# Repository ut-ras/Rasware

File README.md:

# Rasware
Rasware is a generic robotics library project for the EK-LM4F120XL Stellaris Launchpad, built on top of StellarisWare. It is intended to be used for UT RAS's Robotathon competition as well as general purpose robotics projects.
Authored by the IEEE - Robotics and Automation Society Student Branch at the University of Texas at Austin. For documentation, see Rasware's Github [wiki](https://github.com/ut-ras/Rasware/wiki).

---
# Robotathon Setup Instructions
## Get started with Git
1. Create a free GitHub account on [github.com](https://github.com/signup/free)
3. If you want to learn more about Git check out this great beginners guide http://rogerdudler.github.io/git-guide/ or if you really want to get into it, you can read the GitPro book online for free (and legally, too!) at http://git-scm.com/book
## Fork Rasware (only one Robotathon team member should do this step)
1. Once logged into GitHub, go to [ut-ras](https://github.com/ut-ras)'s [Rasware](https://github.com/ut-ras/Rasware).
2. [Fork](https://help.github.com/articles/fork-a-repo) the project's code through the button on the top right. This will copy the project to your own account.
3. On the team's forked repository Github page, go to `Settings -> Collaborators` and add each team member as a collaborator

The remainder of the instructions will depend on what type of system you're running. 

---
## Recommended (Ubuntu VM on VirtualBox)
We have revived RASBox, which is a virtual image already setup and tailored for your Robotathon needs.
### Install VirtualBox
1. Download and install [VirtualBox](https://www.virtualbox.org/wiki/Downloads) for your specific OS.
2. Download the VirtualBox Extension Pack, also on the same page as the VirtualBox dl.
> **NOTE** If the link above doesn't work, try from Oracle's [site](https://www.oracle.com/virtualization/technologies/vm/downloads/virtualbox-downloads.html).
3. Download the RASBox VM from [Google Drive](https://drive.google.com/file/d/1w93RLiauBfxyeFN1s5DmGF2VfKqs-5xN/view?usp=sharing) (2.1GB).
4. Open VirtualBox and go to File > Preferences > Extensions. Add and install the Extension Pack.
5. Import the VM by going to Import and select the .ova file.
6. Click Next and Import. This might take a couple minutes to complete.
> **NOTE** You may need to enable hardware virtualization from your BIOS. See [here](https://bce.berkeley.edu/enabling-virtualization-in-your-pc-bios.html) for help.
7. Go into Settings after the VM has been imported and check to see if any warnings appear. This may be because too many virtual processors or RAM has been allocated to the machine. Adjust as necessary.
    * By default, only 4GB of RAM and 1 processor is in use. The VM will use up to 20 GB of storage, based on your utilization.
8. Start the VM.

### Forward USB Ports
1. Plug in a Launchpad to your computer. If you don't have a Launchpad available, this step can be done later.
2. When the VM is powered off, go to Settings > USB and check to see if the USB with the + icon when clicked upon shows a device for Texas Instruments In-Circuit Debug Interface.
3. If it does not, and you are running Linux/Mac, add yourself to the vboxusers group `sudo usermod -aG vboxusers <USERNAME>`, replacing `<USERNAME>` with your username. You can check who you are with the command `whoami`.
4. Check to see if you're in the group using `groups <USERNAME>`, if vboxusers shows up you're good and should retry step 2.
5. If step 2 continues to fail, restart your computer to enable changes and try again.
6. If you continue to have issues, try consulting [this thread](https://forums.virtualbox.org/viewtopic.php?f=2&t=79254).
7. You can see if your USB device is recognized after starting the VM, running the VM setup script, and checking `/dev/` for a device called `lm4f`.

### Setting up your machine
Once you've followed these steps to a T, start up and log in to the virtual machine (It's preconfigured to log in without the password by default.) The terminal application should start up and ask you to run the post-install script. Once this is completed successfully, you need to setup RASWare. You need to clone your forked repository of Rasware, and then run that setup script. When complete, you should be able to flash RASDemo to your TM4C!
```sh
# post-install script
cd ~/RASBox
sh setup_vm.sh

# rasware setup script
git clone <URL> # <URL> being the git url of your forked Rasware repo
cd ~/RASBox
sh setup_rasware.sh

# Further development instructions can be found at:
code ~/RASBox/RASbox_User_Guide.md
code ~/RASBox/Rasware/RASwareCrashCourse.md
```
---
## I want to make my own VM!
We suggest that if you do want to create your own VM from another distrobution, allocate about 15-20 GB of storage and 4GB of RAM.
The relevant instructions can be found [here](https://www.virtualbox.org/manual/UserManual.html#intro-installing).
## I want to use my existing Mac/Linux machine to develop without a VM.
Please jump to the [Setup For Mac](#Setup-for-Mac) or the [Setup For Linux](#Setup-for-Linux) instructions further below.

---
## Setup for Mac
### Install Dependencies
0. Before we do anything else, run this in your terminal if you're running Marericks or newer (macOS 10.9+) and haven't already done this:

  ```bash
        xcode-select --install
  ```
1. Install Homebrew: [link](http://brew.sh) (Installation instructions are at the bottom of the page.)
2. Install OpenOCD through Homebrew in a terminal.

  ```bash
    brew install openocd
  ```
3. Install the Cross Compiler Toolchain for Embedded ARM Devices through Homebrew as well:

  ```bash
        brew cask install gcc-arm-embedded
  ```
### Configure Groups
1. On macOS devices belong to the `wheel` group, so in order to access the devices on your Mac (like the Launchpad) you also need to be part of the `wheel` group. Put the following in a terminal to see what groups you're part of:

  ```bash
      groups
  ```
2. If `wheel` was one of the groups listed, you're good to go and can skip the next step.
3. If not, add yourself to the `wheel` group:

  ```bash
    sudo dscl . append /Groups/wheel GroupMembership $(whoami)
  ```
### Jump to the Rasware Instructions
1. If everything has worked so far, follow the rest of the instructions on how to use Rasware from the [Setup Rasware](#Setup-Rasware) instructions.

---
## Setup for Linux
These instructions are written for use in a terminal (xterm, gterm, kterm, tty1, etc.) and assume that you have already installed, and are familiar with, your favorite text editor. If you have not found a favorite text editor, I recomend you take a look at [Vim](http://www.vim.org), [Emacs](http://www.emacswiki.org/emacs/), and [SublimeText3](http://www.sublimetext.com/).
### Install Dependencies
1. First install the basic dependencies
* Archlinux : `sudo pacman -S git base-devel openocd screen arm-none-eabi-gcc gdb arm-none-eabi-newlib`
* Ubuntu/Debian : `sudo apt-get install git build-essential openocd screen gcc-arm-none-eabi gdb libnewlib-arm-none-eabi`

---
## Setup Rasware
### Setup a Directory
1. Create a directory to work in. This is where we will place everything.

  ```bash
    mkdir ras
    cd ras
  ```
### Clone Rasware
Use git to clone Rasware, *replacing <USERNAME> with your Git username in the URL.* Make sure you've forked Rasware already!
This makes a copy of Rasware on your computer.

  ```bash
    git clone https://github.com/<USERNAME>/Rasware.git
  ```
### Download StellarisWare
1. Locate Stellarisware, the TI library, in Rasware/Downloads on your computer (in the repository you cloned).
2. Uncompress the file, compile StellarisWare, and move it to `/usr/local/lib`.

  ```bash
    tar vfx StellarisWare.tar.bz2
    cd StellarisWare
    make
    cd ..
    sudo mv StellarisWare /usr/local/lib
    rm StellarisWare.tar.bz2
  ```
### Add the LM4F rule to UDev
> **NOTE**: skip this step if you're on macOS.
1. To avoid needing root access to communicate with the lm4f, you will need to copy the lm4f rule to the udev directory.

  ```bash
    wget https://raw.githubusercontent.com/ut-ras/Rasware/master/RASLib/51-lm4f.rules
    sudo mv 51-lm4f.rules /etc/udev/rules.d
  ```

2. Trigger udev for the new rules to come into effect.

  ```bash
    sudo udevadm control --reload
    sudo udevadm trigger
  ```
> **NOTE**: This may trigger your display to shrink if on a VM. You can fix this by right clicking on the desktop background and rechoosing your display resolution.
3. Plug in a Stellaris Launchpad. you should now see the file `/dev/lm4f`.
### Compile Rasware, RASTemplate, RASDemo
Compile RASLib by using the [make](<https://en.wikipedia.org/wiki/Make_(software)>) program.

  ```bash
    cd Rasware/RASLib
    make
    cd ../RASTemplate
    make
    cd ../RASDemo
    make
  ```
### Compile and run RASDemo
1. We have created an example project to demonstrate Rasware running on a Launchpad.
2. Compile RASDemo.

  ```bash
    cd Rasware/RASDemo
    make
  ```
3. To flash RASDemo to the board, we use make with different arguments.
  ```bash
    make flash
  ```
  You may get an "Error 1" the first time you run this. In this case, simply make flash again. If this doesn't help, next make sure your USB device is connected, powered on, and forwarded to your VM if necessary. If you see "shutdown command invoked," press the reset button. This will start the program on your launchpad. If you keep getting Error 1's, make sure you've forwarded your LaunchPad's USB connection to the VM.
  
  Else, if at this point an error message is printed that includes "Error erasing flash with vFlashErase packet", run the following command twice and press the board's reset button:
  ```bash
    openocd -f $(find /usr -path */scripts/board/*tm4c123* 2>/dev/null) -c init -c halt -c "flash write_image erase RASDemo.out" -c verify_image RASDemo.out -c halt -c shutdown
  ```
  You should now be able to use `make flash` normally until you flash from Keil again. Keil seems to break things. Thank you to Kevin George for this workaround.
4. If a launchpad is plugged in, it should be accessible at a special file in `/dev` (`/dev/lm4f` on Linux, `/dev/tty.usbmodem[board's serial id]` on macOS - run the detect-board script in the RASLib folder if you're curious). You can use make to create a terminal over [UART](https://en.wikipedia.org/wiki/Universal_asynchronous_receiver/transmitter).
  ```bash
    make uart
  ```
5. You should now be presented with the RASDemo menu. Feel free to mess around and look into RASDemo's source code to see how it is done. To exit, you can detach the screen by pressing `C-a d`, or control-A followed by a d. To get back to the launchpad's console, in your terminal run `screen -r`. If you would rather kill the screen process, you can press `C-a k y`, or control-A followed by k then y.
6. If you don't want to do all of the above steps each time, you can run everything with one command.
  ```bash
    make run
  ```
  However, please note opening the console may give an error if the command was already run before and was detached. If this happens, try running `screen -r` in console.

  There's also `make start` which will flash your board and start your program _without_ opening the console.

---
## Committing code back to your repo
1. Before you start, you should configure git with both your username and email.
  ```bash
    git config --global user.name "User Name"
    git config --global user.email "your@email.here"
  ```
2. Git will keep track of any changes to your directory. You can use the status command to show the state of git.
  ```bash
    git status
  ```
3. To stage a file for commiting, you can use the add command.
  ```bash
    git add filename
    git add -all  # stage all files
    git add -u    # only modified and deleted files
  ```
4. You can now use the commit command to create a commit containing all of the modifications of the files you `git add`ed. It will open an editor for writing a [commit message](https://github.com/erlang/otp/wiki/Writing-good-commit-messages). If saved, the commit will be created.
  ```bash
    git commit    # this opens up your default text editor
    git commit -m "Commit messge"   # this doesn't open up your editor
  ```
5. To move your local changes to the server, use the push command.
  ```bash
    git push origin master
  ```

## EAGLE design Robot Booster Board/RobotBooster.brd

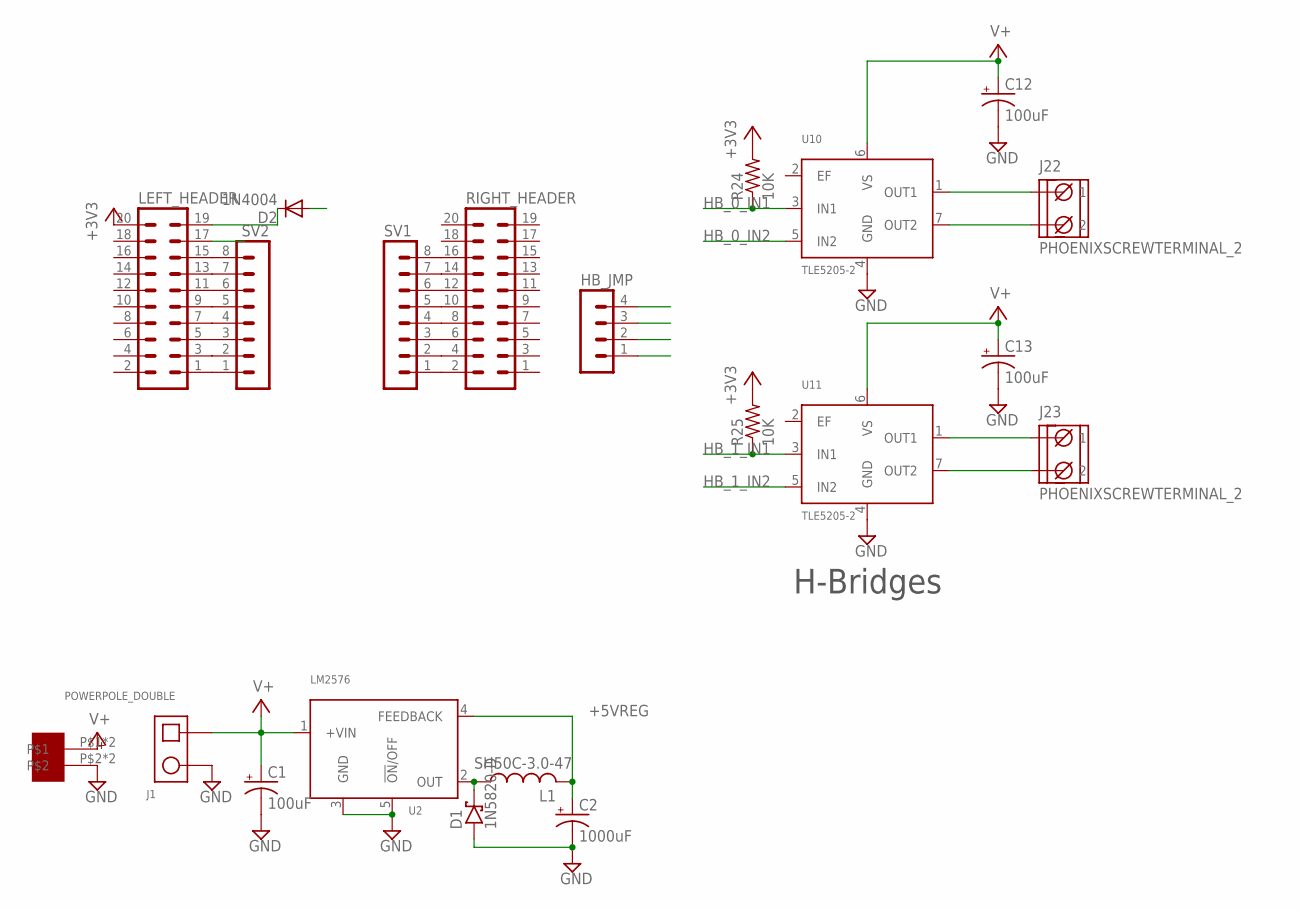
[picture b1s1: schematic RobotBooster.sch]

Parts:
C1, C12, C13: 100uF; E3,5-8
C2: 1000uF; E5-10,5
D1: 1N5820-D; DIODE_17MM
D2: 1N4004; DO41-10
HB_JMP: MA04-1
J1: POWERPOLE_DOUBLE
J22, J23: PHOENIXSCREWTERMINAL_2
L1: SH50C-3.0-47; SH50-C2
LEFT_HEADER: MA10-2
R24, R25: 10K; 0204/5
RIGHT_HEADER: MA10-2
SV1, SV2: MA08-1
U2: LM2576; TO-220-5
U10, U11: TLE5205-2; TO-220-7-11
U$1: .200-2SMD; HLE-108-02-X-DV-BE-A

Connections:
+3V3: LEFT_HEADER.20, R24.2, R25.2
+5VREG: C2.+, D2.A, L1.P$2 (2), U2.4 (FEEDBACK)
GND: C1.-, C2.-, C12.-, C13.-, D1.2 (A), J1.2, LEFT_HEADER.17, U2.3 (GND), U2.5 (!ON!/OFF), U10.4 (GND), U11.4 (GND), U$1.P$2, U$1.P$4
HB_0_IN1: HB_JMP.4, R24.1, U10.3 (IN1)
HB_0_IN2: HB_JMP.3, U10.5 (IN2)
HB_1_IN1: HB_JMP.2, R25.1, U11.3 (IN1)
HB_1_IN2: HB_JMP.1, U11.5 (IN2)
unnamed: D1.1 (C), L1.P$1 (1), U2.2 (OUT)
unnamed: RIGHT_HEADER.2, SV1.1
unnamed: RIGHT_HEADER.4, SV1.2
unnamed: RIGHT_HEADER.6, SV1.3
unnamed: RIGHT_HEADER.8, SV1.4
unnamed: RIGHT_HEADER.10, SV1.5
unnamed: RIGHT_HEADER.12, SV1.6
unnamed: RIGHT_HEADER.14, SV1.7
unnamed: RIGHT_HEADER.16, SV1.8
unnamed: LEFT_HEADER.1, SV2.1
unnamed: LEFT_HEADER.3, SV2.2
unnamed: LEFT_HEADER.5, SV2.3
unnamed: LEFT_HEADER.7, SV2.4
unnamed: LEFT_HEADER.9, SV2.5
unnamed: LEFT_HEADER.11, SV2.6
unnamed: LEFT_HEADER.13, SV2.7
unnamed: LEFT_HEADER.15, SV2.8
unnamed: D2.C, LEFT_HEADER.19
unnamed: J22.1, U10.1 (OUT1)
unnamed: J22.2, U10.7 (OUT2)
unnamed: J23.1, U11.1 (OUT1)
unnamed: J23.2, U11.7 (OUT2)
V+: C1.+, C12.+, C13.+, J1.1, U2.1 (+VIN), U10.6 (VS), U11.6 (VS), U$1.P$1, U$1.P$3

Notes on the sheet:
H-Bridges

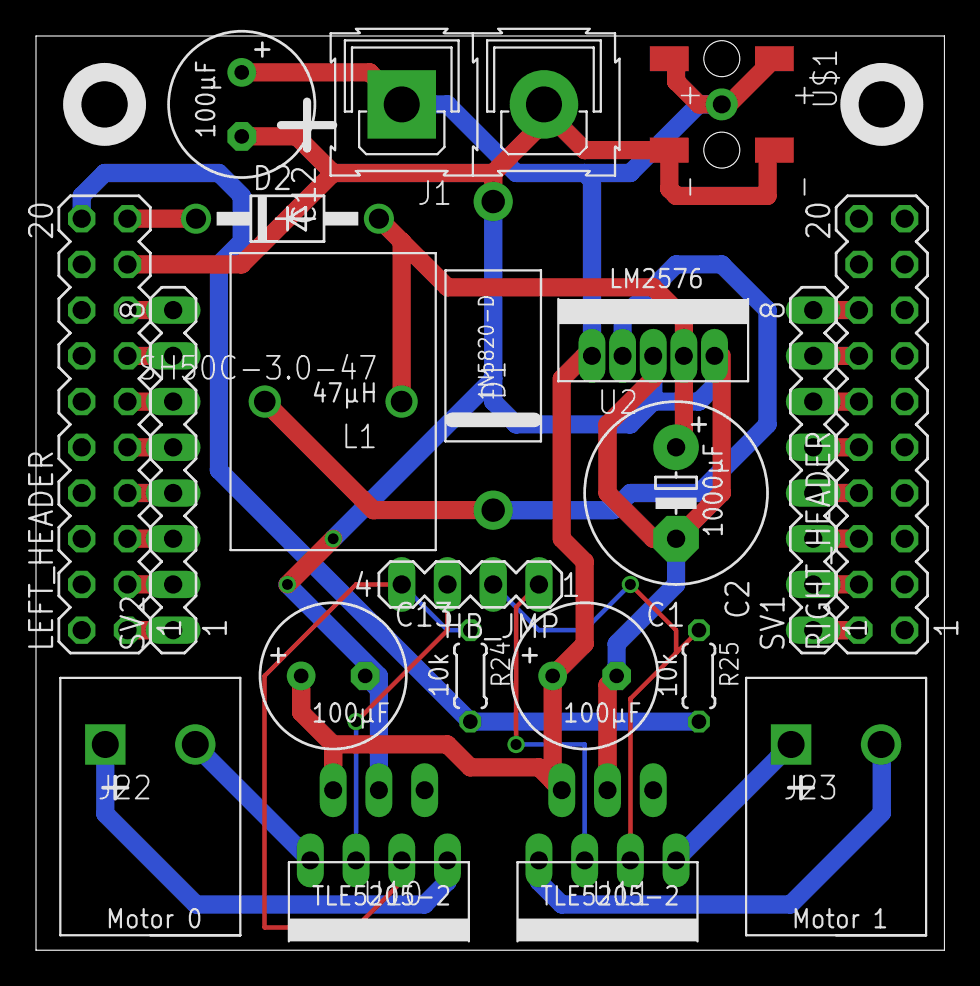
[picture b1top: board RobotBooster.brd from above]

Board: 2 copper layers, 50.5 x 50.8 mm, 21 parts (0 on the bottom side), 30 nets.

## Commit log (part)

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2013-07-29 Added definition for TASK_COUNT
    Represents the number of tasks to allocate internally.
2013-07-30 added blurb about win8 in readme
    Instructions from josh eversmann.
2013-07-30 Fixed small issue with the pending queue in adc
    On removal an element of the pending queue was not having its chain
    broken, which is not checked in later parts of the program.
2013-07-31 Completed implementation of the ordered cyclic pwm
    Requires much testing
2013-08-01 Implemented structs for ordered cyclic pwm and designed basic idea
    Still needs phase/duty cycle implementation
2013-08-05 Reassigned timers used by pwm
    Because pwm is now setup to use all the wide timers, the timers used in time.c were remapped. It now uses Timer 5 as a full 32 bit one shot and the SysTick for clock updates. Unfortunately the SysTic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
2013-08-08 Made file path for uartstdio.c absolute
2013-08-17 Hijacked uartstdio.h to change printf
2013-08-17 Removed old UART usage from Demo
2013-08-21 fixed keil's compiler warnings and added a few more comments
2013-08-23 Repaired formatting with some sed
2013-08-23 Scientific notation support
2013-08-25 Added I2C files and line sensor code, all of which are working
2013-08-25 Made the i2c module modularized to support multiple i2c buses.
2013-08-25 Added wrappers for i2c error handling
    This way error handlind does not require StellarisWare calls unless the
    specific error is needed. The busy wait functions also return if an error
    occurs.
2013-08-25 Reimplemented LineSensor module to match RASLib
    Added background functions and a special function for bit-packed results
    Now matches standardization of RASLib as it stands so far.
    Currently untested.
2013-08-26 added initial rasmath functions
2013-08-26 Response to pull feedback
2013-08-30 added json test, tried to test on real metal, but it including stdio.h appears to be messing things up
2013-08-30 undid changes to raslib's uart.c
2013-08-30 updated comments to reflect initializer change, ran a simple test and saw successful computer->launchpad communication and parsing
2013-08-31 Added timeout recovery code
    The module now recovers from a timeout condition correctly. It can now be
    used without the any connection and properly return an error after every
    call. This has been tested with no attached sensors.
2013-09-02 Made syntactic changes as suggested in the pull request
2013-09-05 inversion works for encoders
2013-09-07 Fixed motor logic
    Was written for high-on logic not low-on logic. Fixed. Also the frequency
    has been moved out of the audible range.
2013-09-09 Tested motors. Found optimal frequency to be roughly 1600hz.
    Also hit 200MHz before induction of motors prevent further testing.
2013-09-09 Fixed range of servos
    Is now in the range of 600us to 2400us like RASWare2012 and checked with a
    servo's datasheet
2013-09-14 added doxygen-style documentation to encoder.h and gpio.h
2013-09-18 Fixed issue with Time handling unused tasks
    UnusedEnd was set to point to the first pointer instead of the end,
    meaning that as soon as a task is returned to the unused pile, all of the
    following tasks are lost.
2013-09-20 Standardized pwm response to invalid data.
    Made it so all of the pwm based functions (motor/servo/pwm) respond to
    invalid data safetly and consistently by not changing their current state.
2013-09-22 changed more pins and formatting
2013-09-24 updated Main bracket placement, added switch statement
2013-09-25 removed unnecessary line in motor.h
2013-10-03 Added GPIO demo and blinky code
2013-10-10 Changed tMotor* array to contain 2 pointers instead of 12
2013-10-17 removed dependnce on UARTstdio
    We used 3 functions from UARTstdio were : UARTgets, UARTputs, and Stdio init.
    all three functions are simple, so I rewrote them.
    I would like to point out that this is primarily to make linking of RASLib easier and to avoid '#include'ing a C source file.
2013-10-19 Cleaned up rasware.
    Removed some unused files, added a few include paths
2013-10-20 Fixed issues with startup file in Keil
    Simple linker issues
    Also had strange issue with INFINITY equality that wasn't revealed until
    now
2013-10-20 Created simple Makefile for cross-compiling with the nescessary libraries.
2013-10-20 updated makefiles to use dependency info generated by gcc
2013-10-20 Made small changes to Makefile and added to README.
    Finally fixed code blocks in README;
    Moved libraries up in Makefiles;
    Changed optimizations to 0 to match Keil;
    Got raslib compiling again.
2013-10-20 Fixed interesting bug with zeroing bss segment
    was overwriting the variables used to do the initializations. Moved
    those into registers. Was interesting because this only happened with
    the optimization level was dropped.
2013-10-23 Update README.md
    - fixed description of `C-a k y` to mention y.
    - removed a would where it was implying something silly
    - added gcc to the dependency lists
    - promoted the install dependencies subsection to a section to match others.
    - added hint/instruction about `make uart`
    - updated `git commit` with a description of how `git add` affects the commit.
2013-10-26 Blinky LED fix
2013-10-27 Pulled RASWare 2012's Line Sensor code in
2013-10-28 Fixed comments
2013-10-30 Changed RASDemo to reflect new RASLib
2013-10-30 added initial pin definitions to sacapuntas.h and changed demo to use those definitions
2013-10-31 renamed LineSensorDemo, fixed inaccurate comment in linesensor.h
2013-11-01 added velocity control header file, sketch
2013-11-03 commented out F1 blinking LED, changed E pins to C pins in the motor demo, added an incremental change option to the motor demo
2013-11-07 Removed second stack
    Keil requires the stack being explicitely created in the Startup file.
    This is fine, except we were creating a second one for the linux port.
2013-11-10 added basic tick-based velocity control code
2013-11-18 Added fix for reseting timers when modifying configuration registers
2013-11-22 added files (again), fixed NavLibTest to compile with new interface changes, now tests vel_control
2013-11-26 created simple waypoint-follower program--no PID
2013-11-26 put math functions in their very own file
2013-11-26 added missing doxygen return description
2013-11-26 add comment about inches
2013-12-01 Added exception catching to close port on error or keyboard interrupt
2013-12-03 Made small changes to readme
2013-12-06 added an include needed to compile i2c module on my system
    this should not cause any issues on anyone else's systems.
    I run Archlinux for reference.
2013-12-10 Recompiled in windows and fixed small issue with using wtimer5 in pwm module
2013-12-10 now vel control runs on units, added two separate sets of pid constants in vel control initialization
2013-12-10 Added TLEMotors to RASDemo
    Tested with both types of motors
2014-01-14 added the servo and tle motor c files to RASLib so that RASDemo will compile without warnings
2014-01-28 changed Servodemo to fix tabs and other nitpicks
2014-01-28 formatting nitpicks on GPIODemo, clarified key press print statement, added newline characters to the end of files
2014-01-28 added usage of printf float support in sonar demo
2014-01-28 fixed nitpicks in UARTDemo
2014-01-28 added some comments to the code
2014-01-28 added spaces to deal with negative signs, initializing charArray with all zeros, found a Printf %s bug
2014-04-04 committing current files
2014-04-11 working code
2014-04-12 Revert "updated speeds"
    This reverts commit 2528dcd7350d278ffd7ee7c03ebdf6d5e199e23b.
2014-06-06 added igvc_code to rasware branch
2014-06-06 make the raslib makefile locations for cortex4mlibs and stellarisware be the same as for igvc_code
2014-09-23 Moved InitializeMCU into Startup.c
    This removes the need to call it upon entering main.
    Advanced usage can modify Startup.c itself.
2014-09-23 implemented some of scanf and all of ungetc
2014-09-24 made length specifiers work;
2014-09-26 GPIO Demo does something reasonable now
    * reads from the whole port
    * skips the parts reserved for the debug uart A[01]
2014-09-28 the uart echos now by default; removed forced echoing
2014-10-04 collapsed Printf calls into one call
2014-10-09 removed unused stuff from scanf and printf
2014-10-09 Fixed something in the scheduler
    Something was going on with the multiple calls to GetTimeUS inside the
    interrupt handler for the scheduler. Not really sure why, but reducing
    this to one calls seems to have solved the issue.
2014-10-10 added drivers folder
2014-10-20 Added MIT license
2014-10-24 Fixed bit logic error in double print hack
2014-11-23 added mac instructions
    courtesy of Soup
2015-03-07 changed toast's ip
2015-03-13 change the name of Ras Ware from 2013 eddition
2015-04-11 fixed last Stellaris include, I hope.
2015-04-16 switched to more portable gpio stuff
2015-07-23 second verse same as the first
2015-07-23 removed old/crap sections from readme
2015-07-23 fixed numbered lists + code blocks maybe
2015-07-23 newlines matter!?
2015-09-02 Changed makefile to use openocd and /usr/local/lib for default paths
2015-09-02 Update README.md
    made the nano example more clear.
2015-09-21 added a SPI module
2015-09-22 fixed stupid bug
2015-10-02 Added newlib dependencies to readme
    arch: arm-none-eabi-newlib
    ubuntu: libnewlib-arm-none-eabi
2015-10-06 Fixed commented out Getc in uart.h
    Was causing some warnings when compiling RASDemo.
2015-10-11 Corrected the ar command to use the arm-none-eabi version
    This fixed the actual issue with indexing symbols in Mac.
2015-10-29 Wall folowing + Servo
2016-09-27 Updated toast's IP address in readme
2016-10-12 Further improved Mac instructions
2017-02-07 Added kilogram's fix from pull request #56
2017-02-07 Revert "Added kilogram's fix from pull request #56"
    This reverts commit 3b8d9bcbd85fb510c8349292aee9ee58599197f7.
2017-02-07 Added workaround for flashing in linux after keil breaks board
2017-08-24 Added Stellarisware tarball to remove dependency on toast.
2017-09-08 One more readme update
2017-09-18 Update openocd script search path/query to support macOS and linux
    openocd on macOS (when installed with brew) stores its board scripts in /usr/local/Cellar/open-ocd/...
    openocd on Linux uses /usr/share/openocd/...
    Searching /usr for */scripts/board/*tm4c123* should work for both OSes and is pretty safe (very unlikely to find and use something that isn't really the TM4C board script).
    The 2>/dev/null at the end of the find command is there to suppress permissions errors.
2017-09-18 Propagate makefile changes
2017-09-18 One last README.md change for macOS users (wheel)
2017-09-21 Apparently VMWare requires VT-x on Windows 10.
2017-09-23 Fix permissions on detect-board script. (my bad)
2017-10-04 Formatting oopsies
2017-10-12 IR sensor clarification
2018-09-30 Updated Ubuntu image download location.
2018-10-07 Add WSL support to detect-board
    Three things that still need be resolved/investigated:
    - /run/screen (?) needs to be set to 777 and this requires sudo; not sure if this is a one time thing
    - the detect-board routine for WSL is not very robust; it'll likely choke on multiple devices
    - ICDI drivers; not sure if required as mentioned earlier
    Other than that, things are looking shiny!
2018-10-07 Add rules for RASLib
2018-10-07 fix file permisions while I still can
2018-10-07 win-install.sh should be done
2018-10-07 Speed detect-board up a little bit (caching)
2020-07-02 Updated and cleaned README.md
